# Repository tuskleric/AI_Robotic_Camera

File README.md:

# pico_fyp

Make sure to create an enviroment variable called PICO_SDK_PATH which is a relitive path to wherever your pico-sdk folder is stored

## Getting started

To make it easy for you to get started with GitLab, here's a list of recommended next steps.

Already a pro? Just edit this README.md and make it your own. Want to make it easy? [Use the template at the bottom](#editing-this-readme)!

## Add your files

- [ ] [Create](https://docs.gitlab.com/ee/user/project/repository/web_editor.html#create-a-file) or [upload](https://docs.gitlab.com/ee/user/project/repository/web_editor.html#upload-a-file) files
- [ ] [Add files using the command line](https://docs.gitlab.com/ee/gitlab-basics/add-file.html#add-a-file-using-the-command-line) or push an existing Git repository with the following command:

```

```

## Integrate with your tools

- [ ] [Set up project integrations](https://eng-git.canterbury.ac.nz/jsu109/pico_fyp/-/settings/integrations)

## Collaborate with your team

- [ ] [Invite team members and collaborators](https://docs.gitlab.com/ee/user/project/members/)
- [ ] [Create a new merge request](https://docs.gitlab.com/ee/user/project/merge_requests/creating_merge_requests.html)
- [ ] [Automatically close issues from merge requests](https://docs.gitlab.com/ee/user/project/issues/managing_issues.html#closing-issues-automatically)
- [ ] [Enable merge request approvals](https://docs.gitlab.com/ee/user/project/merge_requests/approvals/)
- [ ] [Set auto-merge](https://docs.gitlab.com/ee/user/project/merge_requests/merge_when_pipeline_succeeds.html)

## Test and Deploy

Use the built-in continuous integration in GitLab.

- [ ] [Get started with GitLab CI/CD](https://docs.gitlab.com/ee/ci/quick_start/index.html)
- [ ] [Analyze your code for known vulnerabilities with Static Application Security Testing (SAST)](https://docs.gitlab.com/ee/user/application_security/sast/)
- [ ] [Deploy to Kubernetes, Amazon EC2, or Amazon ECS using Auto Deploy](https://docs.gitlab.com/ee/topics/autodevops/requirements.html)
- [ ] [Use pull-based deployments for improved Kubernetes management](https://docs.gitlab.com/ee/user/clusters/agent/)
- [ ] [Set up protected environments](https://docs.gitlab.com/ee/ci/environments/protected_environments.html)

***

# Editing this README

When you're ready to make this README your own, just edit this file and use the handy template below (or feel free to structure it however you want - this is just a starting point!). Thanks to [makeareadme.com](https://www.makeareadme.com/) for this template.

## Suggestions for a good README

Every project is different, so consider which of these sections apply to yours. The sections used in the template are suggestions for most open source projects. Also keep in mind that while a README can be too long and detailed, too long is better than too short. If you think your README is too long, consider utilizing another form of documentation rather than cutting out information.

## Name
Choose a self-explaining name for your project.

## Description
Let people know what your project can do specifically. Provide context and add a link to any reference visitors might be unfamiliar with. A list of Features or a Background subsection can also be added here. If there are alternatives to your project, this is a good place to list differentiating factors.

## Badges
On some READMEs, you may see small images that convey metadata, such as whether or not all the tests are passing for the project. You can use Shields to add some to your README. Many services also have instructions for adding a badge.

## Visuals
Depending on what you are making, it can be a good idea to include screenshots or even a video (you'll frequently see GIFs rather than actual videos). Tools like ttygif can help, but check out Asciinema for a more sophisticated method.

## Installation
Within a particular ecosystem, there may be a common way of installing things, such as using Yarn, NuGet, or Homebrew. However, consider the possibility that whoever is reading your README is a novice and would like more guidance. Listing specific steps helps remove ambiguity and gets people to using your project as quickly as possible. If it only runs in a specific context like a particular programming language version or operating system or has dependencies that have to be installed manually, also add a Requirements subsection.

## Usage
Use examples liberally, and show the expected output if you can. It's helpful to have inline the smallest example of usage that you can demonstrate, while providing links to more sophisticated examples if they are too long to reasonably include in the README.

## Support
Tell people where they can go to for help. It can be any combination of an issue tracker, a chat room, an email address, etc.

## Roadmap
If you have ideas for releases in the future, it is a good idea to list them in the README.

## Contributing
State if you are open to contributions and what your requirements are for accepting them.

For people who want to make changes to your project, it's helpful to have some documentation on how to get started. Perhaps there is a script that they should run or some environment variables that they need to set. Make these steps explicit. These instructions could also be useful to your future self.

You can also document commands to lint the code or run tests. These steps help to ensure high code quality and reduce the likelihood that the changes inadvertently break something. Having instructions for running tests is especially helpful if it requires external setup, such as starting a Selenium server for testing in a browser.

## Authors and acknowledgment
Show your appreciation to those who have contributed to the project.

## License
For open source projects, say how it is licensed.

## Project status
If you have run out of energy or time for your project, put a note at the top of the README saying that development has slowed down or stopped completely. Someone may choose to fork your project or volunteer to step in as a maintainer or owner, allowing your project to keep going. You can also make an explicit request for maintainers.

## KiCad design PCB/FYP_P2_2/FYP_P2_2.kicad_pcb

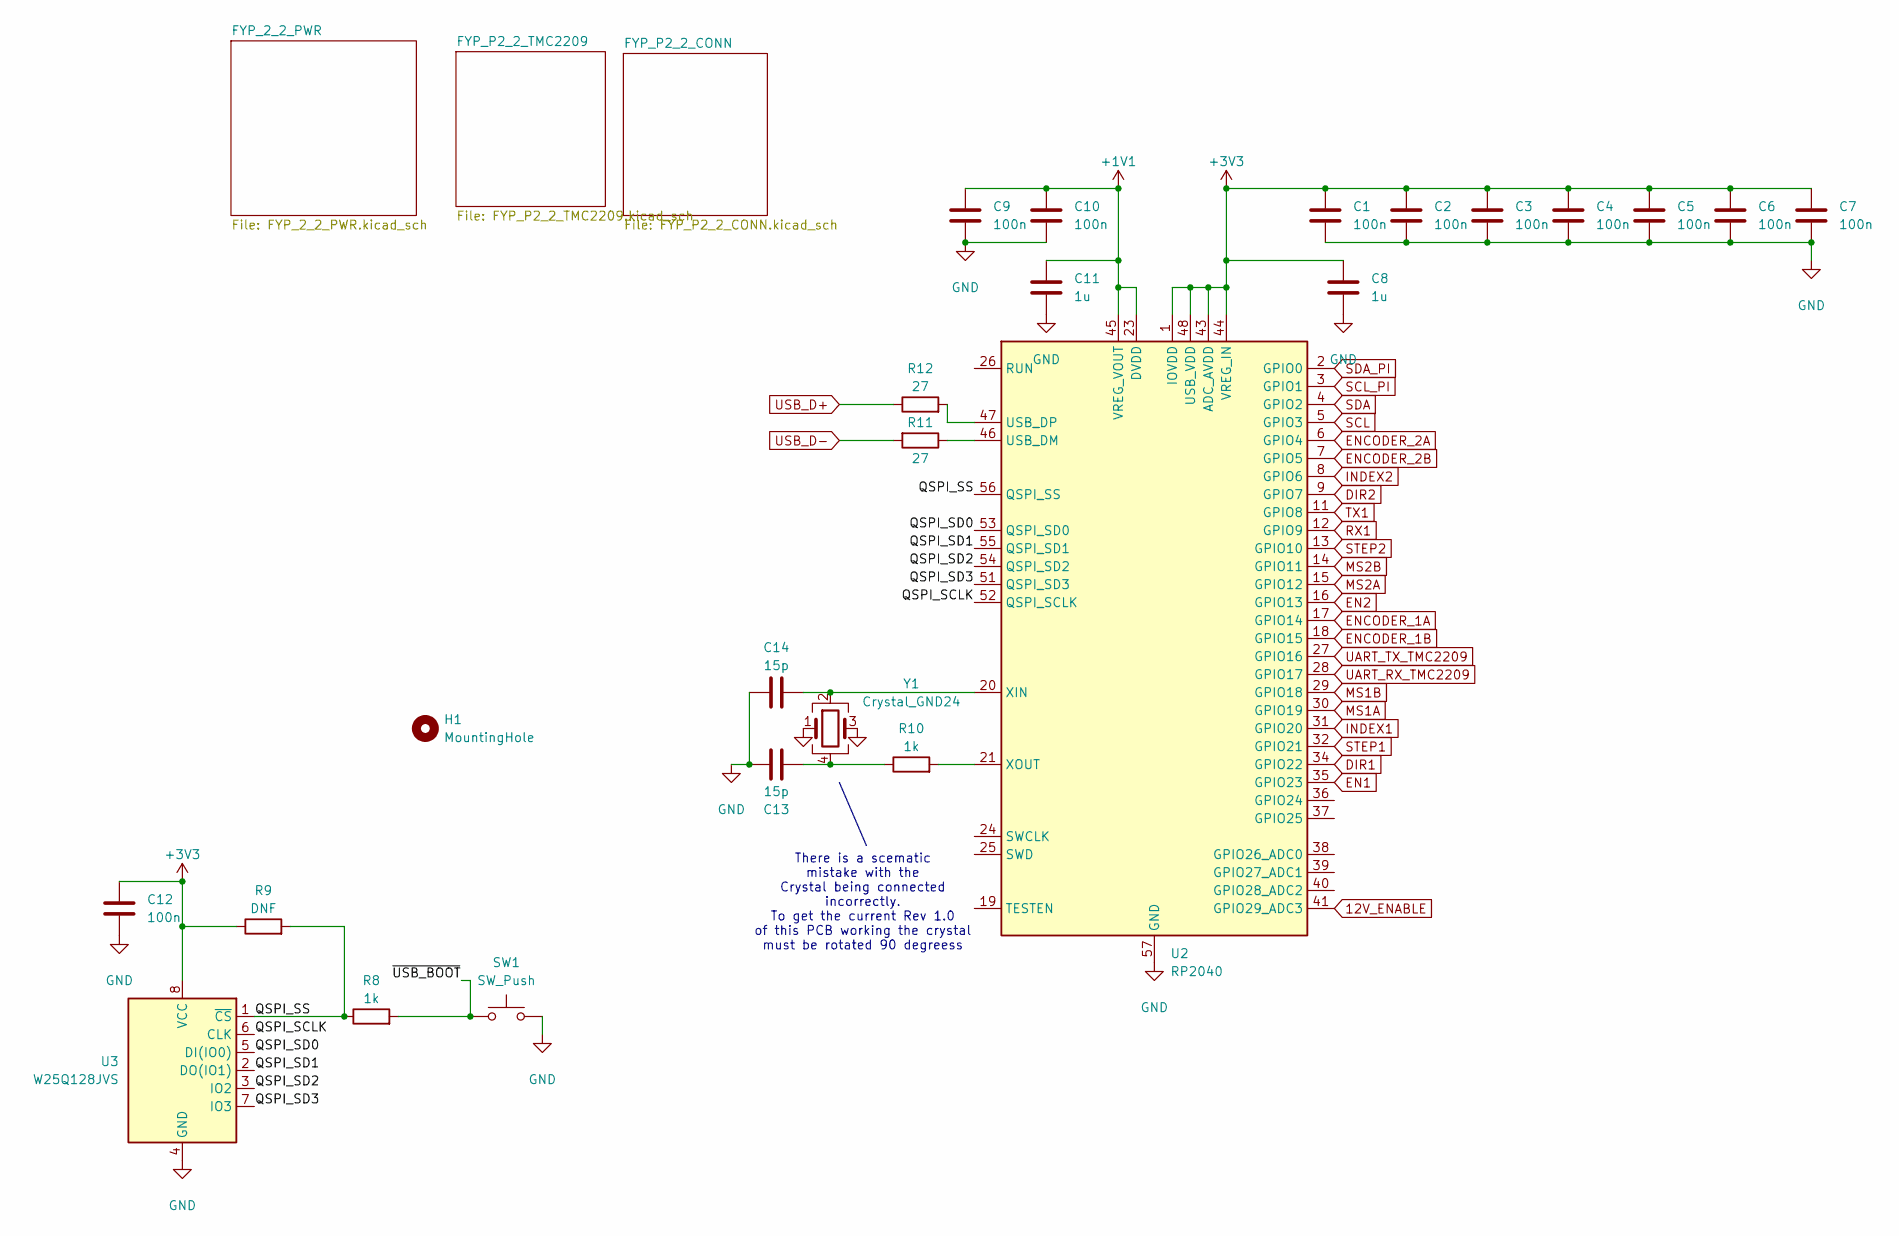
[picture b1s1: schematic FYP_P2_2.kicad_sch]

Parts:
C1, C2, C3, C4, C5, C6, C7, C9, C10, C12: 100n; C_0603_1608Metric
C8, C11: 1u; C_0603_1608Metric
C13, C14: 15p; C_0603_1608Metric
H1: MountingHole; MountingHole_2.2mm_M2
R8, R10: 1k; R_0603_1608Metric
R9: DNF; R_0603_1608Metric
R11, R12: 27; R_0603_1608Metric
SW1: SW_Push; SW_Push_1P1T_NO_CK_KMR2
U2: RP2040; QFN-56-1EP_7x7mm_P0.4mm_EP3.2x3.2mm
U3: W25Q128JVS; SOIC-8_5.23x5.23mm_P1.27mm
Y1: Crystal_GND24; Crystal_SMD_3225-4Pin_3.2x2.5mm

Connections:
12V_ENABLE: U2.41 (GPIO29_ADC3); also elsewhere on the board
+1V1: C9.1, C10.1, C11.1, U2.23 (DVDD), U2.45 (VREG_VOUT), U2.50 (DVDD)
+3V3: C1.1, C2.1, C3.1, C4.1, C5.1, C6.1, C7.1, C8.1, C12.1, R9.1, U2.1 (IOVDD), U2.10 (IOVDD), U2.22 (IOVDD), U2.33 (IOVDD), U2.42 (IOVDD), U2.43 (ADC_AVDD), U2.44 (VREG_IN), U2.48 (USB_VDD), U2.49 (IOVDD), U3.8 (VCC); also elsewhere on the board
/QSPI_SCLK: U2.52 (QSPI_SCLK), U3.6 (CLK)
/QSPI_SD0: U2.53 (QSPI_SD0), U3.5 (DI(IO0))
/QSPI_SD1: U2.55 (QSPI_SD1), U3.2 (DO(IO1))
/QSPI_SD2: U2.54 (QSPI_SD2), U3.3 (IO2)
/QSPI_SD3: U2.51 (QSPI_SD3), U3.7 (IO3)
/QSPI_SS: R8.1, R9.2, U2.56 (QSPI_SS), U3.1 (~CS)
/~USB_BOOT: R8.2, SW1.1
DIR1: U2.34 (GPIO22); also elsewhere on the board
DIR2: U2.9 (GPIO7); also elsewhere on the board
EN1: U2.35 (GPIO23); also elsewhere on the board
EN2: U2.16 (GPIO13); also elsewhere on the board
ENCODER_1A: U2.17 (GPIO14); also elsewhere on the board
ENCODER_1B: U2.18 (GPIO15); also elsewhere on the board
ENCODER_2A: U2.6 (GPIO4); also elsewhere on the board
ENCODER_2B: U2.7 (GPIO5); also elsewhere on the board
GND: C1.2, C2.2, C3.2, C4.2, C5.2, C6.2, C7.2, C8.2, C9.2, C10.2, C11.2, C12.2, C13.1, C14.2, SW1.2, U2.57 (GND), U3.4 (GND), Y1.1, Y1.3; also elsewhere on the board
INDEX1: U2.31 (GPIO20); also elsewhere on the board
INDEX2: U2.8 (GPIO6); also elsewhere on the board
MS1A: U2.30 (GPIO19); also elsewhere on the board
MS1B: U2.29 (GPIO18); also elsewhere on the board
MS2A: U2.15 (GPIO12); also elsewhere on the board
MS2B: U2.14 (GPIO11); also elsewhere on the board
unnamed: C13.2, R10.1, Y1.4
unnamed: R11.1, U2.46 (USB_DM)
unnamed: R12.2, U2.47 (USB_DP)
unnamed: C14.1, U2.20 (XIN), Y1.2
unnamed: R10.2, U2.21 (XOUT)
RX1: U2.12 (GPIO9); also elsewhere on the board
SCL: U2.5 (GPIO3); also elsewhere on the board
SCL_PI: U2.3 (GPIO1); also elsewhere on the board
SDA: U2.4 (GPIO2); also elsewhere on the board
SDA_PI: U2.2 (GPIO0); also elsewhere on the board
STEP1: U2.32 (GPIO21); also elsewhere on the board
STEP2: U2.13 (GPIO10); also elsewhere on the board
TX1: U2.11 (GPIO8); also elsewhere on the board
UART_RX_TMC2209: U2.28 (GPIO17); also elsewhere on the board
UART_TX_TMC2209: U2.27 (GPIO16); also elsewhere on the board
USB_D+: R12.1; also elsewhere on the board
USB_D-: R11.2; also elsewhere on the board

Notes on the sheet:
There is a scematic mistake with the Crystal being connected incorrectly. To get the current Rev 1.0 of this PCB working the crystal must be rotated 90 degreess

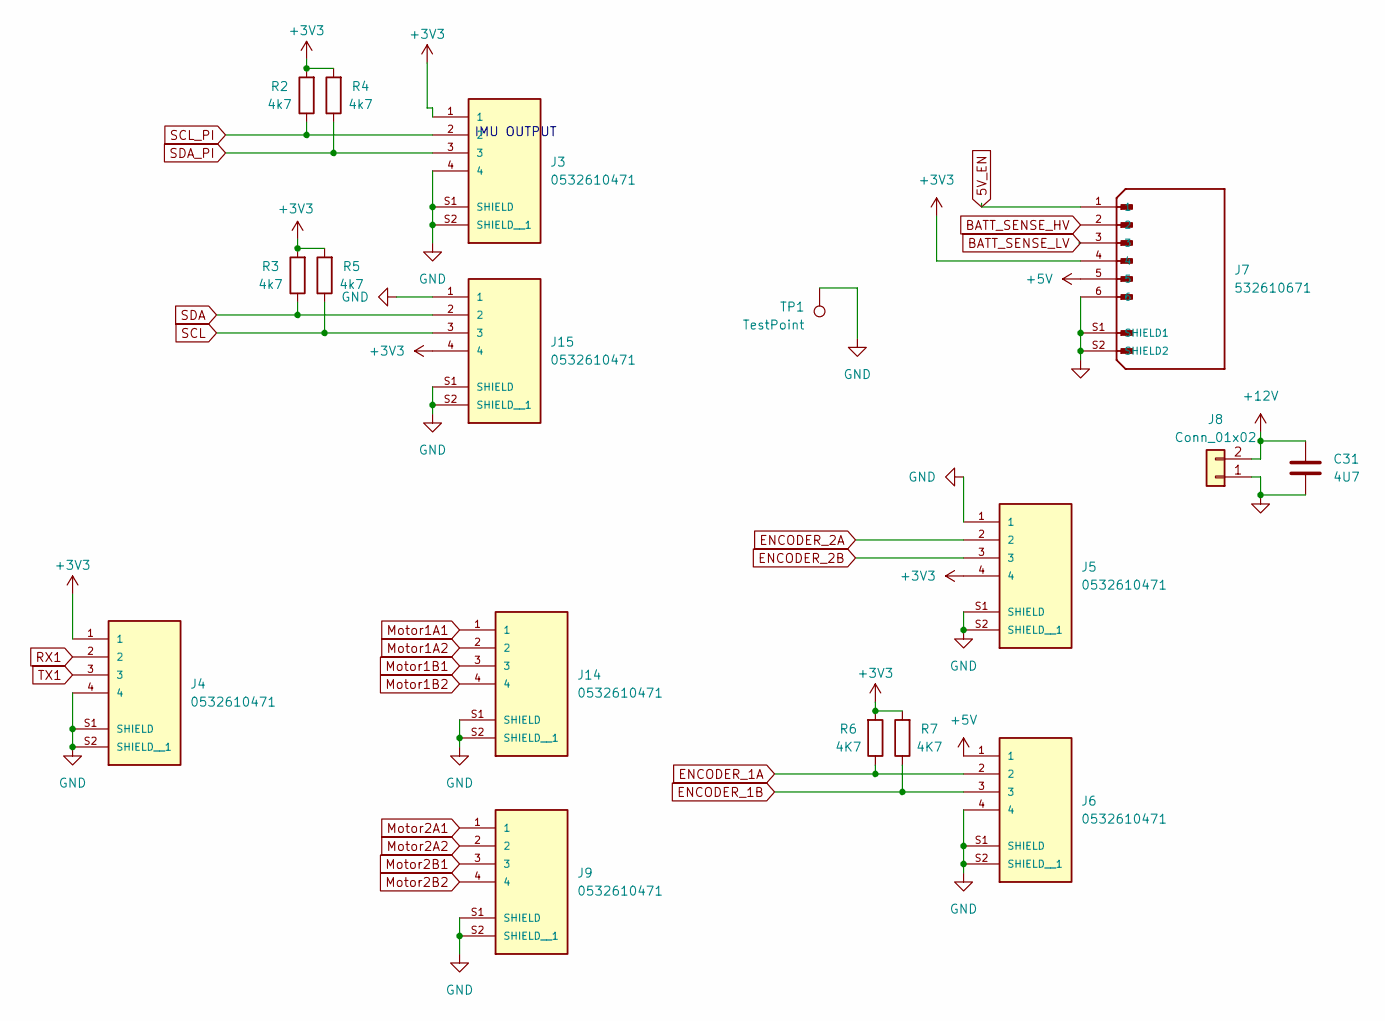
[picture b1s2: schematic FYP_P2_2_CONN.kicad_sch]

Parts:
C31: 4U7; C_0603_1608Metric
J3, J4, J5, J6, J9, J14, J15: 0532610471; MOLEX_0532610471; PARTREV J
J7: 532610671; MOLEX_532610671; PARTREV J
J8: Conn_01x02; PinHeader_1x02_P2.54mm_Horizontal
R2, R3, R4, R5: 4k7; R_0603_1608Metric
R6, R7: 4K7; R_0603_1608Metric
TP1: TestPoint; TestPoint_Pad_1.5x1.5mm

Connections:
5V_EN: J7.1; also elsewhere on the board
+3V3: J3.1, J4.1, J5.4, J7.4, J15.4, R2.2, R3.2, R4.2, R5.2, R6.2, R7.2; also elsewhere on the board
+5V: J6.1, J7.5; also elsewhere on the board
+12V: C31.1, J8.2; also elsewhere on the board
BATT_SENSE_HV: J7.2; also elsewhere on the board
BATT_SENSE_LV: J7.3; also elsewhere on the board
ENCODER_1A: J6.2, R6.1; also elsewhere on the board
ENCODER_1B: J6.3, R7.1; also elsewhere on the board
ENCODER_2A: J5.2; also elsewhere on the board
ENCODER_2B: J5.3; also elsewhere on the board
GND: C31.2, J3.4, J3.S1 (SHIELD), J3.S2 (SHIELD__1), J4.4, J4.S1 (SHIELD), J4.S2 (SHIELD__1), J5.1, J5.S1 (SHIELD), J5.S2 (SHIELD__1), J6.4, J6.S1 (SHIELD), J6.S2 (SHIELD__1), J7.6, J7.S1 (SHIELD1), J7.S2 (SHIELD2), J8.1, J9.S1 (SHIELD), J9.S2 (SHIELD__1), J14.S1 (SHIELD), J14.S2 (SHIELD__1), J15.1, J15.S1 (SHIELD), J15.S2 (SHIELD__1), TP1.1; also elsewhere on the board
Motor1A1: J14.1; also elsewhere on the board
Motor1A2: J14.2; also elsewhere on the board
Motor1B1: J14.3; also elsewhere on the board
Motor1B2: J14.4; also elsewhere on the board
Motor2A1: J9.1; also elsewhere on the board
Motor2A2: J9.2; also elsewhere on the board
Motor2B1: J9.3; also elsewhere on the board
Motor2B2: J9.4; also elsewhere on the board
RX1: J4.2; also elsewhere on the board
SCL: J15.3, R5.1; also elsewhere on the board
SCL_PI: J3.2, R2.1; also elsewhere on the board
SDA: J15.2, R3.1; also elsewhere on the board
SDA_PI: J3.3, R4.1; also elsewhere on the board
TX1: J4.3; also elsewhere on the board

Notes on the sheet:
IMU OUTPUT

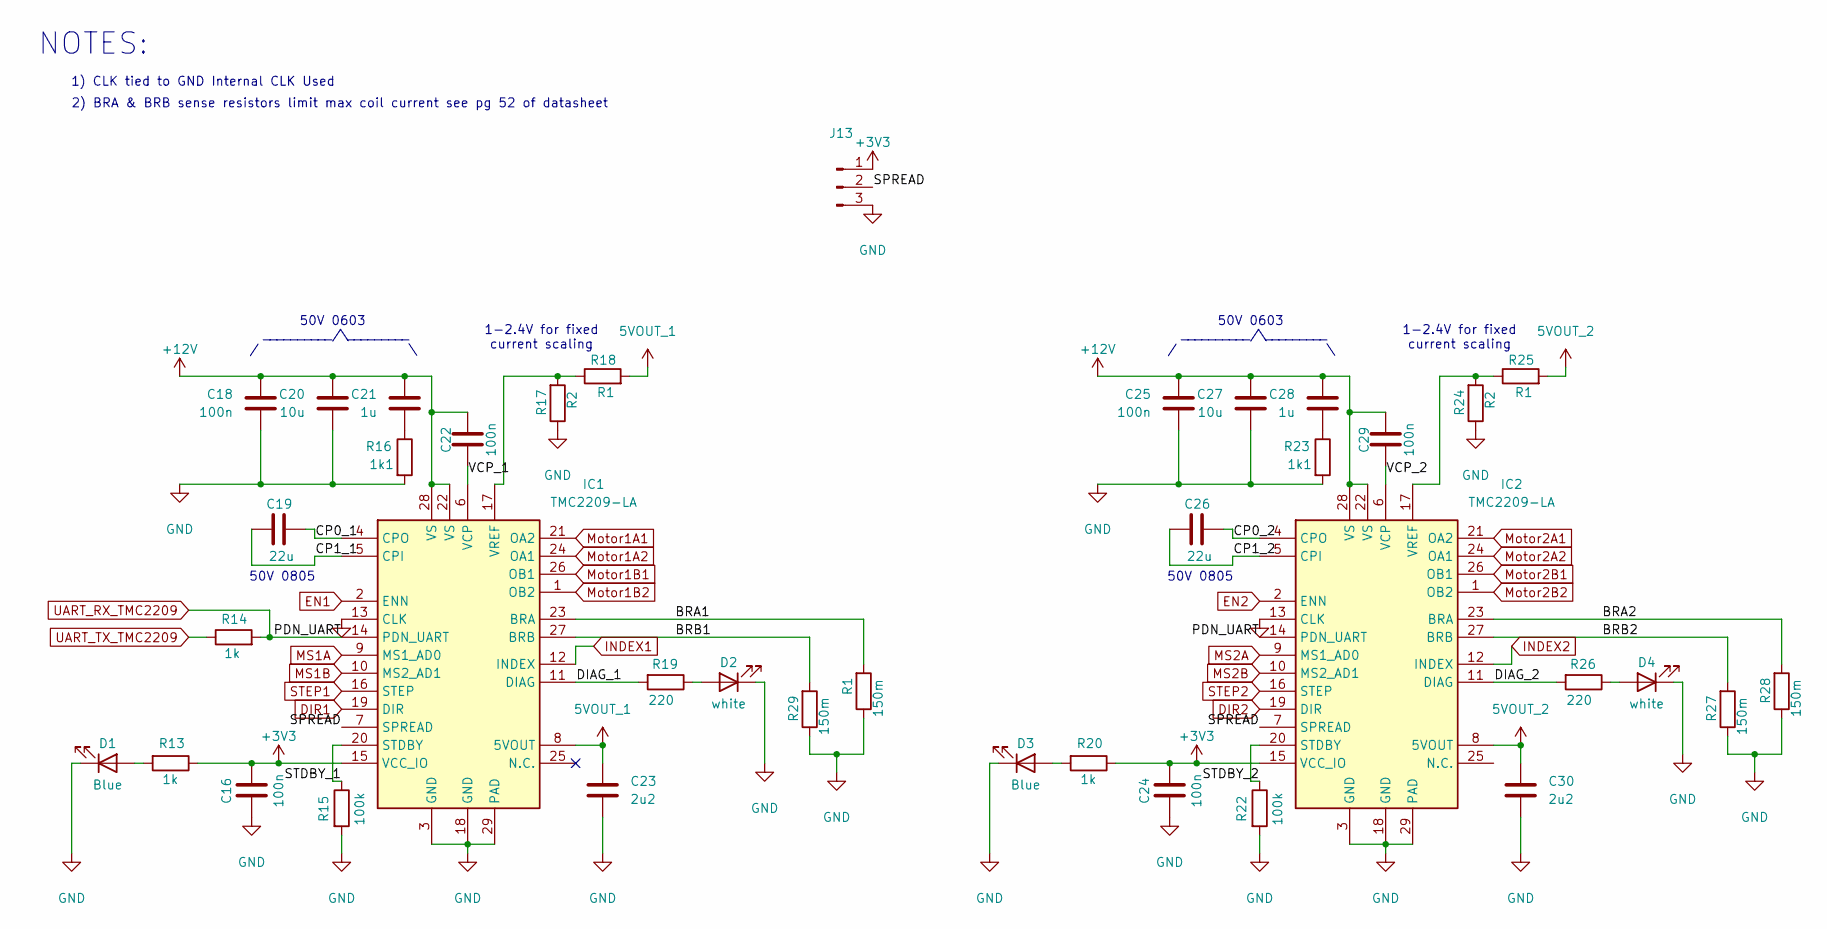
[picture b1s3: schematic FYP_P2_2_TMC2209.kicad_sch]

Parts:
C16, C18, C22, C24, C25, C29: 100n; C_0603_1608Metric
C19, C26: 22u; C_0603_1608Metric
C20, C27: 10u; C_0805_2012Metric
C21, C28: 1u; C_0603_1608Metric
C23, C30: 2u2; C_0603_1608Metric
D1, D3: Blue; LED_0603_1608Metric
D2, D4: white; LED_0603_1608Metric
IC1, IC2: TMC2209-LA; QFN50P500X500X90-29N; Manufacturer_Part_Number TMC2209-LA; Mouser Part Number 700-TMC2209-LA
J13: Conn_01x03_Pin; SolderJumper-3_P1.3mm_Open_Pad1.0x1.5mm
R1, R27, R28, R29: 150m; R_1206_3216Metric
R13, R14, R20: 1k; R_0603_1608Metric
R15, R22: 100k; R_0603_1608Metric
R16, R23: 1k1; R_0603_1608Metric
R17, R24: R2; R_0603_1608Metric
R18, R25: R1; R_0603_1608Metric
R19, R26: 220; R_0603_1608Metric

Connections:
5VOUT_1: C23.1, IC1.8 (5VOUT), R18.2
5VOUT_2: C30.1, IC2.8 (5VOUT), R25.2
+3V3: C16.1, C24.1, IC1.15 (VCC_IO), IC2.15 (VCC_IO), J13.1, R13.1, R20.1; also elsewhere on the board
+12V: C18.1, C20.1, C21.1, C22.1, C25.1, C27.1, C28.1, C29.1, IC1.22 (VS), IC1.28 (VS), IC2.22 (VS), IC2.28 (VS); also elsewhere on the board
/FYP_P2_2_TMC2209/BRA1: IC1.23 (BRA), R1.2
/FYP_P2_2_TMC2209/BRA2: IC2.23 (BRA), R28.2
/FYP_P2_2_TMC2209/BRB1: IC1.27 (BRB), R29.2
/FYP_P2_2_TMC2209/BRB2: IC2.27 (BRB), R27.2
/FYP_P2_2_TMC2209/CP0_1: C19.2, IC1.4 (CPO)
/FYP_P2_2_TMC2209/CP0_2: C26.2, IC2.4 (CPO)
/FYP_P2_2_TMC2209/CP1_1: C19.1, IC1.5 (CPI)
/FYP_P2_2_TMC2209/CP1_2: C26.1, IC2.5 (CPI)
/FYP_P2_2_TMC2209/DIAG_1: IC1.11 (DIAG), R19.2
/FYP_P2_2_TMC2209/DIAG_2: IC2.11 (DIAG), R26.2
/FYP_P2_2_TMC2209/SPREAD: IC1.7 (SPREAD), IC2.7 (SPREAD), J13.2
/FYP_P2_2_TMC2209/STDBY_1: IC1.20 (STDBY), R15.1
/FYP_P2_2_TMC2209/STDBY_2: IC2.20 (STDBY), R22.1
/FYP_P2_2_TMC2209/VCP_1: C22.2, IC1.6 (VCP)
/FYP_P2_2_TMC2209/VCP_2: C29.2, IC2.6 (VCP)
DIR1: IC1.19 (DIR); also elsewhere on the board
DIR2: IC2.19 (DIR); also elsewhere on the board
EN1: IC1.2 (ENN); also elsewhere on the board
EN2: IC2.2 (ENN); also elsewhere on the board
GND: C16.2, C18.2, C20.2, C23.2, C24.2, C25.2, C27.2, C30.2, D1.1 (K), D2.1 (K), D3.1 (K), D4.1 (K), IC1.3 (GND), IC1.13 (CLK), IC1.18 (GND), IC1.29 (PAD), IC2.3 (GND), IC2.13 (CLK), IC2.18 (GND), IC2.29 (PAD), J13.3, R1.1, R15.2, R16.2, R17.1, R22.2, R23.2, R24.1, R27.1, R28.1, R29.1; also elsewhere on the board
INDEX1: IC1.12 (INDEX); also elsewhere on the board
INDEX2: IC2.12 (INDEX); also elsewhere on the board
MS1A: IC1.9 (MS1_AD0); also elsewhere on the board
MS1B: IC1.10 (MS2_AD1); also elsewhere on the board
MS2A: IC2.9 (MS1_AD0); also elsewhere on the board
MS2B: IC2.10 (MS2_AD1); also elsewhere on the board
Motor1A1: IC1.21 (OA2); also elsewhere on the board
Motor1A2: IC1.24 (OA1); also elsewhere on the board
Motor1B1: IC1.26 (OB1); also elsewhere on the board
Motor1B2: IC1.1 (OB2); also elsewhere on the board
Motor2A1: IC2.21 (OA2); also elsewhere on the board
Motor2A2: IC2.24 (OA1); also elsewhere on the board
Motor2B1: IC2.26 (OB1); also elsewhere on the board
Motor2B2: IC2.1 (OB2); also elsewhere on the board
unnamed: C21.2, R16.1
unnamed: C28.2, R23.1
unnamed: D1.2 (A), R13.2
unnamed: D2.2 (A), R19.1
unnamed: D3.2 (A), R20.2
unnamed: D4.2 (A), R26.1
unnamed: IC1.17 (VREF), R17.2, R18.1
unnamed: IC2.17 (VREF), R24.2, R25.1
STEP1: IC1.16 (STEP); also elsewhere on the board
STEP2: IC2.16 (STEP); also elsewhere on the board
UART_RX_TMC2209: IC1.14 (PDN_UART), IC2.14 (PDN_UART), R14.2; also elsewhere on the board
UART_TX_TMC2209: R14.1; also elsewhere on the board

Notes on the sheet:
1-2.4V for fixed current scaling
2) BRA & BRB sense resistors limit max coil current see pg 52 of datasheet
50V 0603 __________/\_________ / \
50V 0805
NOTES:
1) CLK tied to GND Internal CLK Used

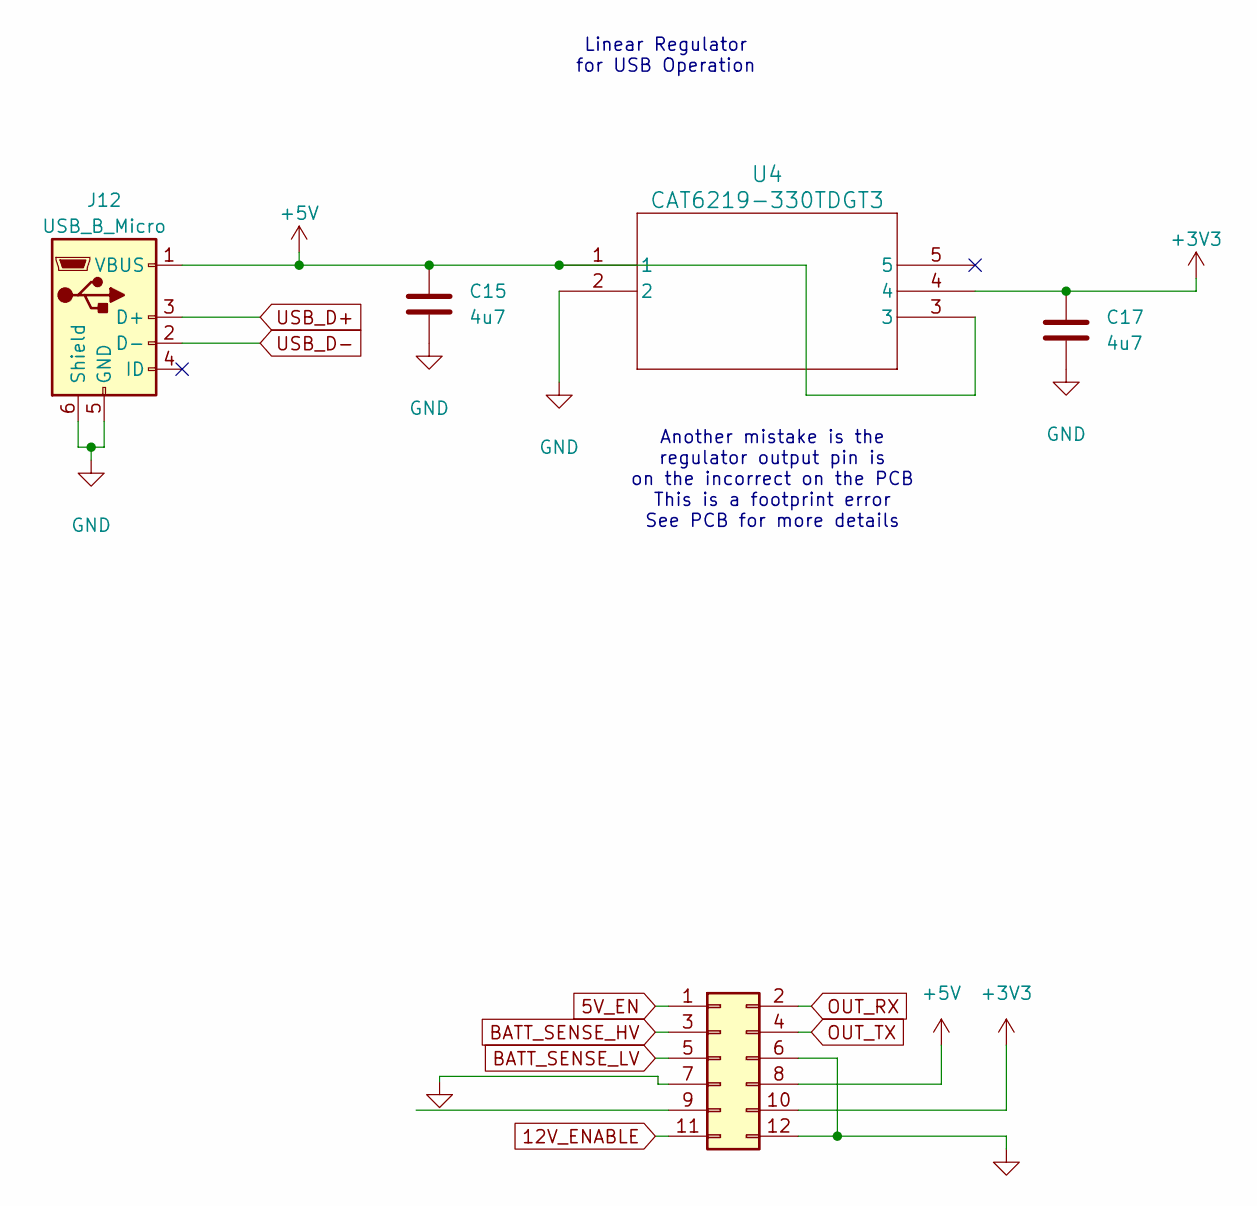
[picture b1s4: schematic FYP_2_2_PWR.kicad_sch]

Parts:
C15, C17: 4u7; C_0603_1608Metric
J2: Conn_02x06_Odd_Even; PinSocket_2x06_P2.00mm_Vertical_SMD; Digikey 2073-BF060-12A-B-0600-0280-0305-L-D-ND
J12: USB_B_Micro; USB_Micro-B_Amphenol_10103594-0001LF_Horizontal
U4: CAT6219-330TDGT3; TSOT23-5_ONS

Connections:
5V_EN: J2.1; also elsewhere on the board
12V_ENABLE: J2.11; also elsewhere on the board
+3V3: C17.1, J2.10, U4.4; also elsewhere on the board
+5V: C15.1, J2.8, J12.1 (VBUS), U4.1, U4.3; also elsewhere on the board
BATT_SENSE_HV: J2.3; also elsewhere on the board
BATT_SENSE_LV: J2.5; also elsewhere on the board
GND: C15.2, C17.2, J2.6, J2.7, J2.12, J12.5 (GND), J12.6 (Shield), U4.2; also elsewhere on the board
OUT_RX: J2.2
OUT_TX: J2.4
USB_D+: J12.3 (D+); also elsewhere on the board
USB_D-: J12.2 (D-); also elsewhere on the board

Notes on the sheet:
Another mistake is the regulator output pin is on the incorrect on the PCB This is a footprint error See PCB for more details
Linear Regulator for USB Operation

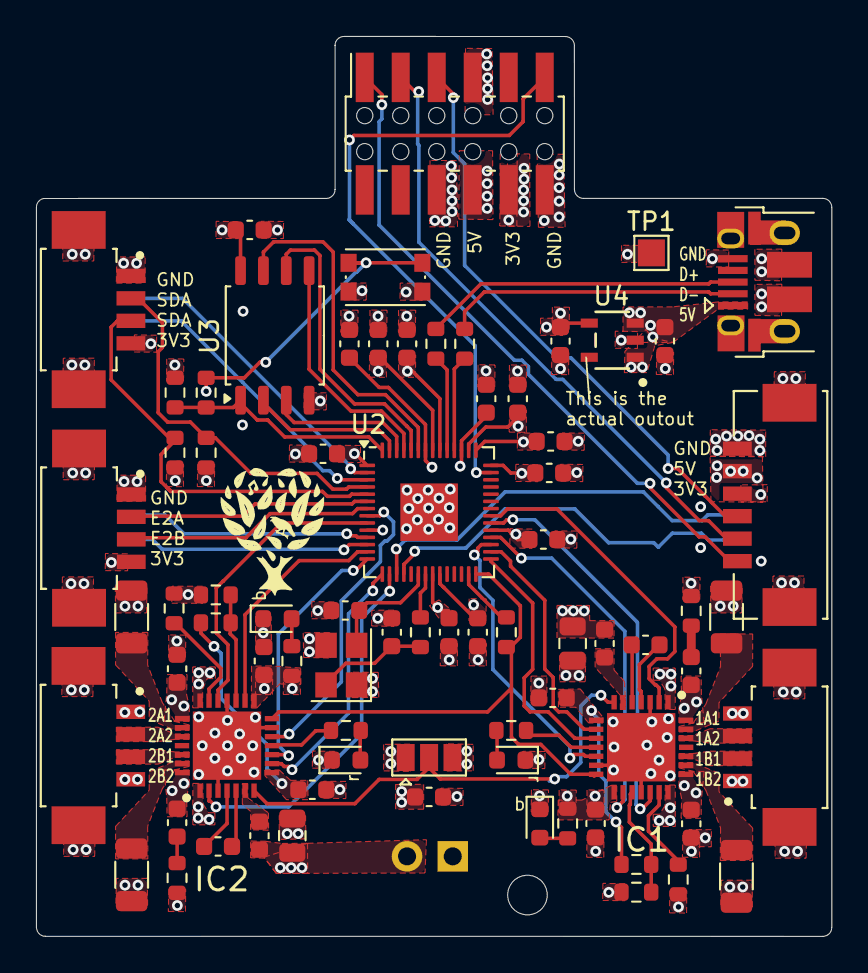
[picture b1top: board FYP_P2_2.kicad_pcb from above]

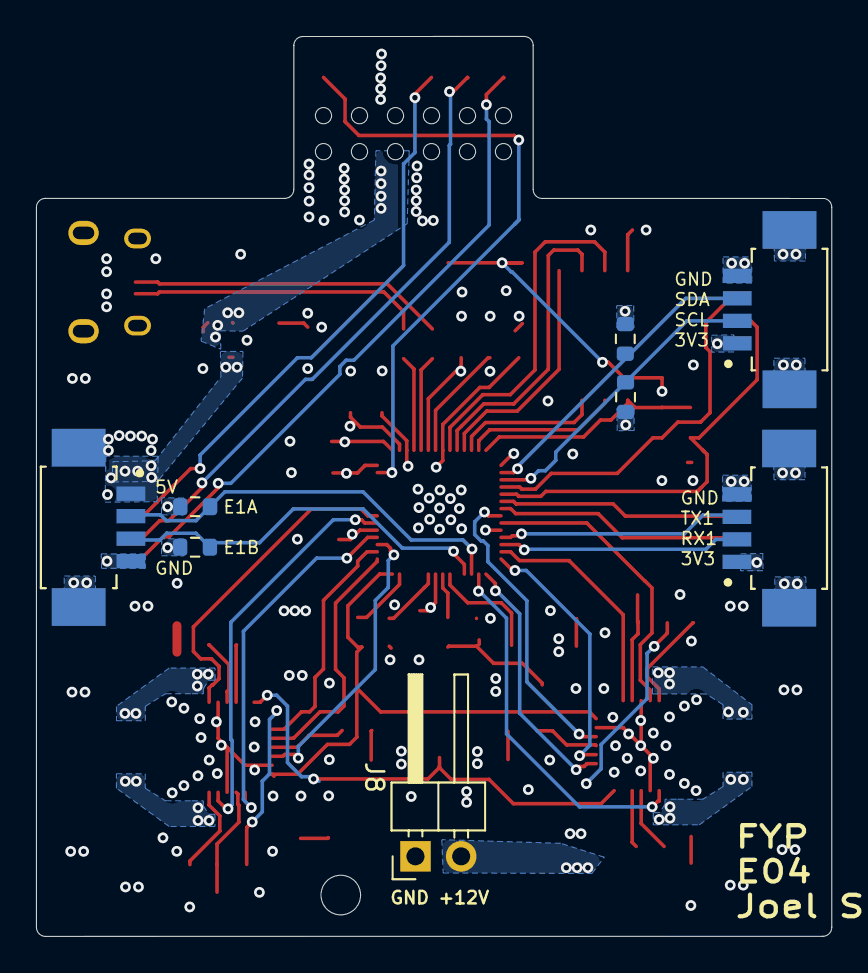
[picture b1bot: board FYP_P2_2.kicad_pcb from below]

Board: 4 copper layers, 44.2 x 50.0 mm, 84 parts (8 on the bottom side), 80 nets.

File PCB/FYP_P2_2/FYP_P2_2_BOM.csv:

Reference,Value,Rating,Datasheet,Footprint,Qty,DNP,Digikey
C1 C2 C3 C4 C5 C6 C7 C9 C10 C12 C16 C18 C22 C24 C25 C29,100n,50V,~,Capacitor_SMD:C_0603_1608Metric,16,,
C8,1u,16V,~,Capacitor_SMD:C_0603_1608Metric,1,,
C11 C21 C28,1u,50V,~,Capacitor_SMD:C_0603_1608Metric,3,,
C13 C14,15p,50V,~,Capacitor_SMD:C_0603_1608Metric,2,,
C15 C17,4u7,16V,~,Capacitor_SMD:C_0603_1608Metric,2,,
C19 C26,22u,50V,~,Capacitor_SMD:C_0603_1608Metric,2,,
C20 C27,10u,50V,~,Capacitor_SMD:C_0805_2012Metric,2,,
C23 C30,2u2,16V,~,Capacitor_SMD:C_0603_1608Metric,2,,
C31,4U7,16V,~,Capacitor_SMD:C_0603_1608Metric,1,,
D1 D3,Blue,Light emitting diode,~,LED_SMD:LED_0603_1608Metric,2,,
D2 D4,white,Light emitting diode,~,LED_SMD:LED_0603_1608Metric,2,,
IC1 IC2,TMC2209-LA,Silent stepper motor driver 5 to 36V,https://www.analog.com/media/en/technical-documentation/data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,TMC2209-LA:QFN50P500X500X90-29N,2,,
J2,Conn_02x06_Odd_Even,,~,Connector_PinSocket_2.00mm:PinSocket_2x06_P2.00mm_Vertical_SMD,1,,
J3 J4 J5 J6 J9 J14 J15,532610471,,,0532610471:MOLEX_0532610471,7,,
J7,532610671,,,0532610671:MOLEX_532610671,1,,
J8,Conn_01x02,,~,Connector_PinHeader_2.54mm:PinHeader_1x02_P2.54mm_Horizontal,1,,
J12,USB_B_Micro,USB Micro Type B connector,~,Connector_USB:USB_Micro-B_Amphenol_10103594-0001LF_Horizontal,1,,
J13,Conn_01x03_Pin,Generic connector,~,Jumper:SolderJumper-3_P1.3mm_Open_Pad1.0x1.5mm,1,,
R1 R27 R28 R29,150m,Resistor,~,Resistor_SMD:R_1206_3216Metric,4,,
R2 R3 R4 R5,4k7,Resistor,~,Resistor_SMD:R_0603_1608Metric,4,,
R6 R7,4K7,Resistor,~,Resistor_SMD:R_0603_1608Metric,2,,
R8 R10 R13 R14 R20,1k,Resistor,~,Resistor_SMD:R_0603_1608Metric,5,,
R9,DNF,Resistor,~,Resistor_SMD:R_0603_1608Metric,1,,
R11 R12,27,Resistor,~,Resistor_SMD:R_0603_1608Metric,2,,
R15 R22,100k,Resistor,~,Resistor_SMD:R_0603_1608Metric,2,,
R16 R23,1k1,Resistor,~,Resistor_SMD:R_0603_1608Metric,2,,
R17 R24,R2,Resistor,~,Resistor_SMD:R_0603_1608Metric,2,,
R18 R25,R1,Resistor,~,Resistor_SMD:R_0603_1608Metric,2,,
R19 R26,220,Resistor,~,Resistor_SMD:R_0603_1608Metric,2,,
SW1,SW_Push,Push button switch,~,Button_Switch_SMD:SW_Push_1P1T_NO_CK_KMR2,1,,
TP1,TestPoint,,~,TestPoint:TestPoint_Pad_1.5x1.5mm,1,,
U2,RP2040,A microcontroller by Raspberry Pi,https://datasheets.raspberrypi.com/rp2040/rp2040-datasheet.pdf,Package_DFN_QFN:QFN-56-1EP_7x7mm_P0.4mm_EP3.2x3.2mm,1,,
U3,W25Q128JVS,128Mb Serial Flash Memory,http://www.winbond.com/resource-files/w25q128jv_dtr%20revc%2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,Package_SO:SOIC-8_5.23x5.23mm_P1.27mm,1,,
U4,CAT6219-330TDGT3,,CAT6219-330TDGT3,SV_CAT6219-330TDGT3:TSOT23-5_ONS,1,,
Y1,Crystal_GND24,Four pin crystal,~,Crystal:Crystal_SMD_3225-4Pin_3.2x2.5mm,1,,

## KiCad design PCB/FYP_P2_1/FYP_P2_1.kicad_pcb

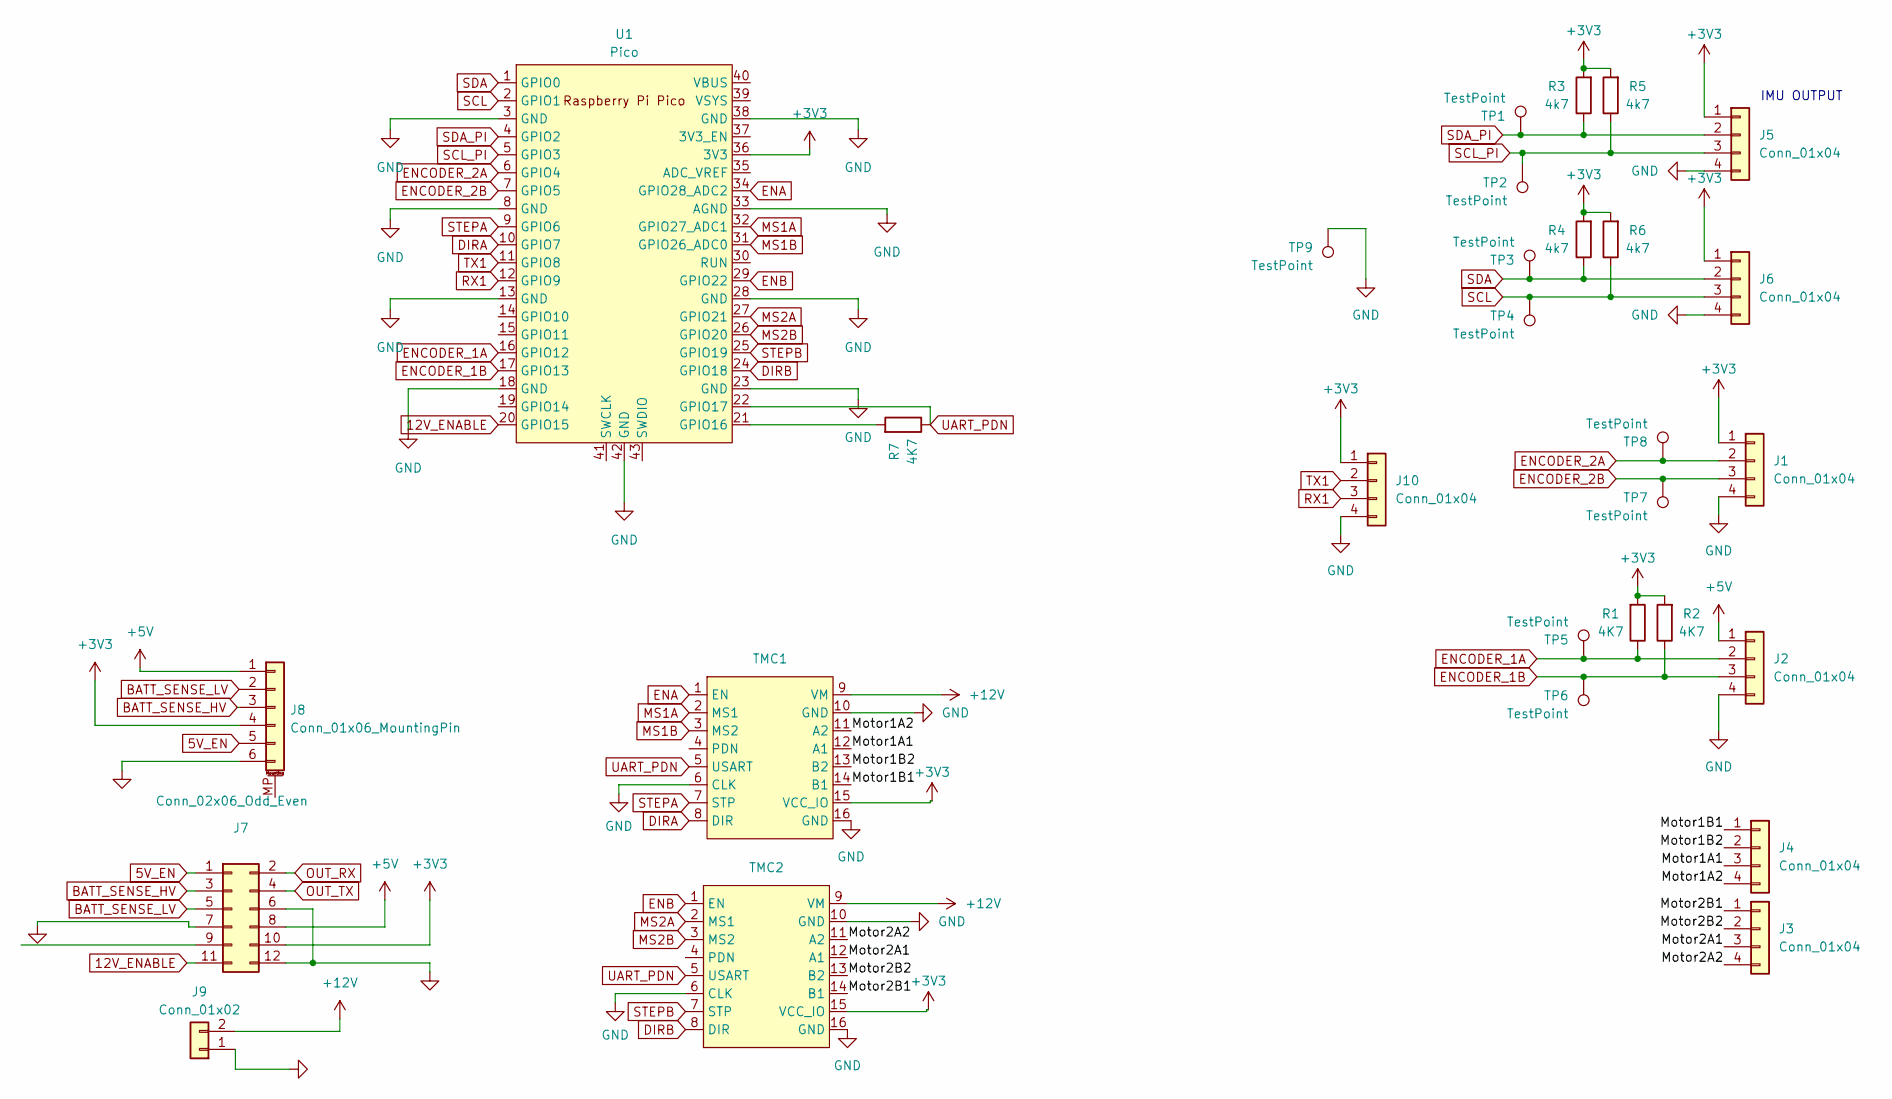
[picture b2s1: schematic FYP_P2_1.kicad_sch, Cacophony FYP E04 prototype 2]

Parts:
J1, J2, J3, J4, J5, J6, J10: Conn_01x04; JST_XH_S4B-XH-A_1x04_P2.50mm_Horizontal
J7: Conn_02x06_Odd_Even; PinSocket_2x06_P2.00mm_Vertical_SMD; Digikey 2073-BF060-12A-B-0600-0280-0305-L-D-ND
J8: Conn_01x06_MountingPin; JST_XH_S6B-XH-A-1_1x06_P2.50mm_Horizontal
J9: Conn_01x02; CON_1719740002_MOL
R1, R2, R7: 4K7; R_0603_1608Metric
R3, R4, R5, R6: 4k7; R_0603_1608Metric
TMC1, TMC2: MODULE_TMC2209_SILENTSTEPSTICK
TP1, TP2, TP3, TP4, TP5, TP6, TP7, TP8, TP9: TestPoint; TestPoint_Pad_1.5x1.5mm
U1: Pico; PICO

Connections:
5V_EN: J7.1, J8.5
12V_ENABLE: J7.11, U1.20 (GPIO15)
+3V3: J1.1, J5.1, J6.1, J7.10, J8.4, J10.1, R1.2, R2.2, R3.2, R4.2, R5.2, R6.2, TMC1.15 (VCC_IO), TMC2.15 (VCC_IO), U1.36 (3V3)
+5V: J2.1, J7.8, J8.1
+12V: J9.2, TMC1.9 (VM), TMC2.9 (VM)
/Motor1A1: J4.3, TMC1.12 (A1)
/Motor1A2: J4.4, TMC1.11 (A2)
/Motor1B1: J4.1, TMC1.14 (B1)
/Motor1B2: J4.2, TMC1.13 (B2)
/Motor2A1: J3.3, TMC2.12 (A1)
/Motor2A2: J3.4, TMC2.11 (A2)
/Motor2B1: J3.1, TMC2.14 (B1)
/Motor2B2: J3.2, TMC2.13 (B2)
BATT_SENSE_HV: J7.3, J8.3
BATT_SENSE_LV: J7.5, J8.2
DIRA: TMC1.8 (DIR), U1.10 (GPIO7)
DIRB: TMC2.8 (DIR), U1.24 (GPIO18)
ENA: TMC1.1 (EN), U1.34 (GPIO28_ADC2)
ENB: TMC2.1 (EN), U1.29 (GPIO22)
ENCODER_1A: J2.2, R1.1, TP5.1, U1.16 (GPIO12)
ENCODER_1B: J2.3, R2.1, TP6.1, U1.17 (GPIO13)
ENCODER_2A: J1.2, TP8.1, U1.6 (GPIO4)
ENCODER_2B: J1.3, TP7.1, U1.7 (GPIO5)
GND: J1.4, J2.4, J3.6, J3.7, J3.12, J5.4, J6.4, J7.6, J7.7, J7.12, J8.6, J9.1, J10.4, TMC1.6 (CLK), TMC1.10 (GND), TMC1.16 (GND), TMC2.6 (CLK), TMC2.10 (GND), TMC2.16 (GND), TP9.1, U1.3 (GND), U1.8 (GND), U1.13 (GND), U1.18 (GND), U1.23 (GND), U1.28 (GND), U1.33 (AGND), U1.38 (GND), U1.42 (GND); also elsewhere on the board
MS1A: TMC1.2 (MS1), U1.32 (GPIO27_ADC1)
MS1B: TMC1.3 (MS2), U1.31 (GPIO26_ADC0)
MS2A: TMC2.2 (MS1), U1.27 (GPIO21)
MS2B: TMC2.3 (MS2), U1.26 (GPIO20)
unnamed: R7.2, U1.21 (GPIO16)
OUT_RX: J7.2
OUT_TX: J7.4
RX1: J10.3, U1.12 (GPIO9)
SCL: J6.3, R6.1, TP4.1, U1.2 (GPIO1)
SCL_PI: J5.3, R5.1, TP2.1, U1.5 (GPIO3)
SDA: J6.2, R4.1, TP3.1, U1.1 (GPIO0)
SDA_PI: J5.2, R3.1, TP1.1, U1.4 (GPIO2)
STEPA: TMC1.7 (STP), U1.9 (GPIO6)
STEPB: TMC2.7 (STP), U1.25 (GPIO19)
TX1: J10.2, U1.11 (GPIO8)
UART_PDN: R7.1, TMC1.5 (USART), TMC2.5 (USART), U1.22 (GPIO17)

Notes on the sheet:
IMU OUTPUT

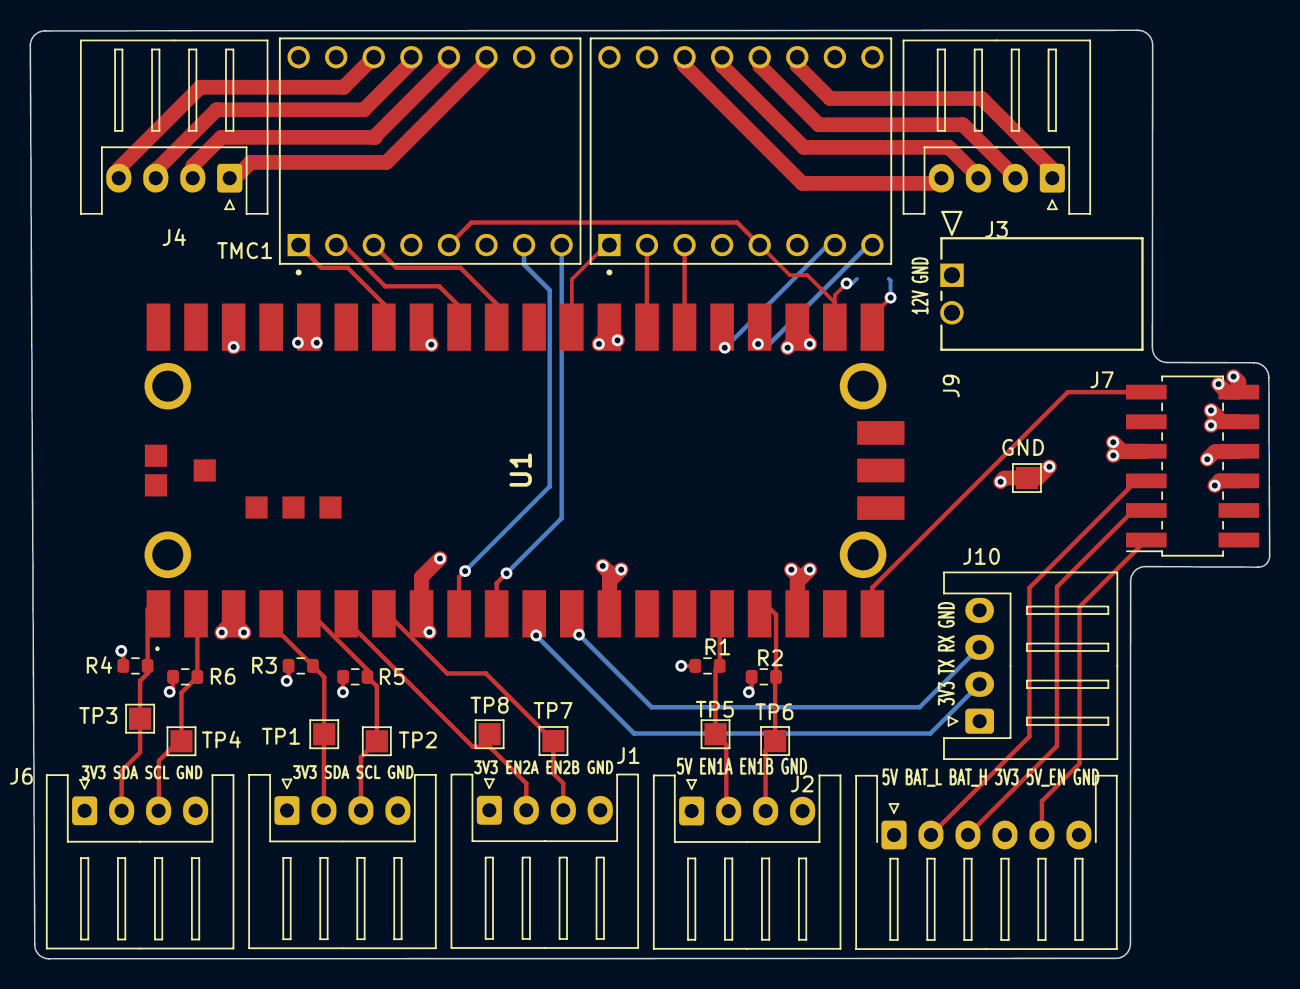
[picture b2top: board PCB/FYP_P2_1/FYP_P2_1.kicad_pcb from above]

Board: 4 copper layers, 83.8 x 62.8 mm, 29 parts (1 on the bottom side), 38 nets.

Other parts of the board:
GND: TestPoint; TestPoint_Pad_1.5x1.5mm

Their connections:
GND: GND.1; also elsewhere on the board
